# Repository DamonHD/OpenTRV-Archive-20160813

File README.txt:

WARNING: AS OF 2016/08/13 THIS IS A READ-ONLY ARCHIVE/SNAPSHOT WITH HISTORY

See https://github.com/opentrv/OTWiki/wiki/Repo-Restructure-2016-08-13
for how the content has been refactored.

This is the OpenTRV (Open-Source Thermostatic Radiator Valve) project.

See http://www.earth.org.uk/open-source-programmable-thermostatic-radiator-valve.html for more.

Contains software and hardware elements.

Note that the content of this project is available under a permissive licence,
Apache 2.0 or (Solderpad 0.51 for hardware elements) unless otherwise stated,
and is provided supplied AS-IS with no warranties of any kind.

Fragments of contributed code, libraries, etc, within here may have their own licences,
in which case that should be explicit in each case.

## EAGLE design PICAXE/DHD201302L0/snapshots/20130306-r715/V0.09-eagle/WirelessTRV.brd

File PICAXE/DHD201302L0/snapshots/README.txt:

Snapshots of software/hardware at significant development stages.

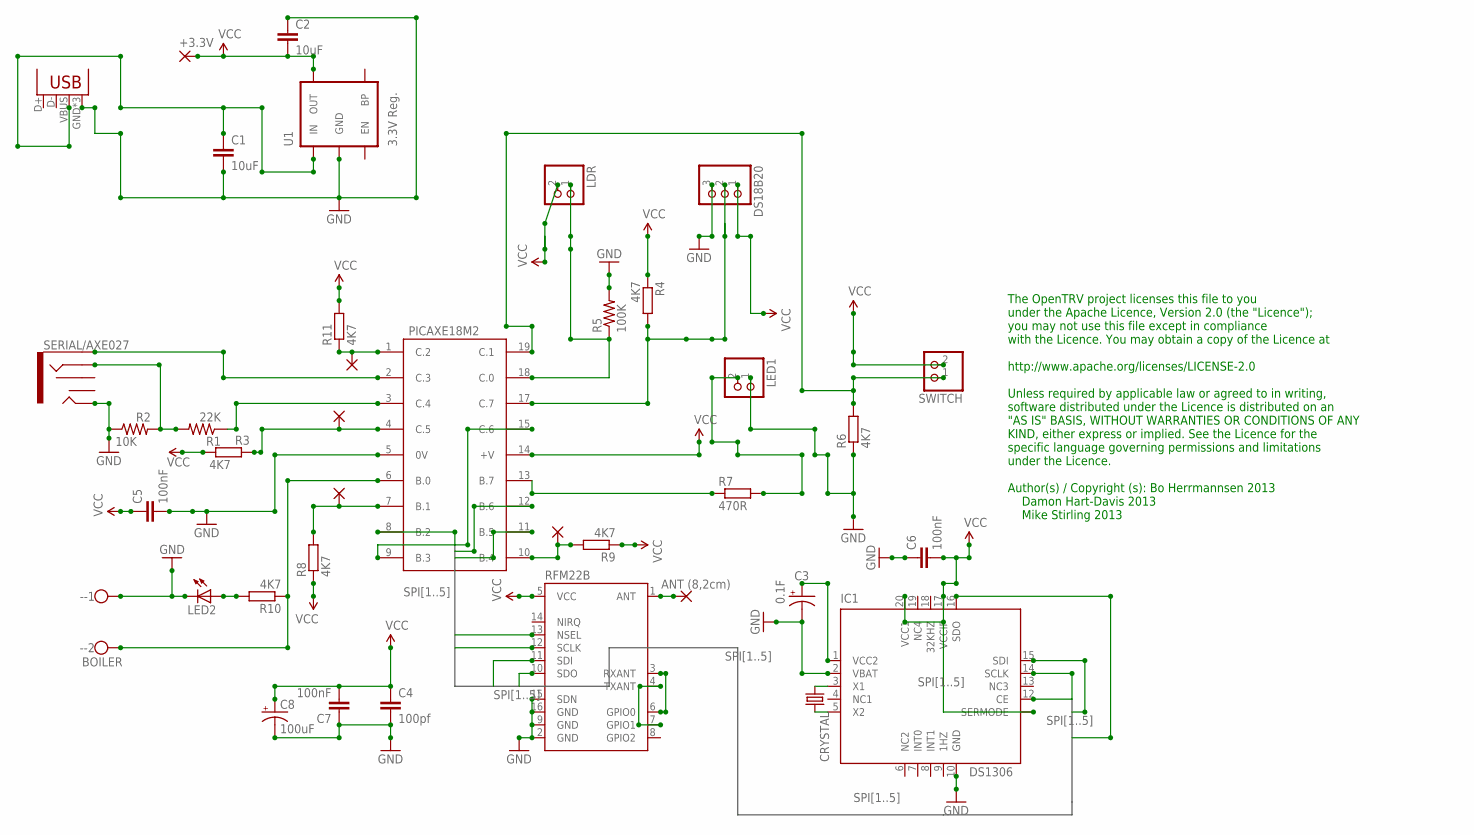
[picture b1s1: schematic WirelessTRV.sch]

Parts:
1, 4, 7, 10: 2,15/1,0
5V: USB-MICROB
+3.3V: 2,15/1,0
-: BOILER; W237-102
ANT: ANT (8,2cm); 2,15/1,0
C1, C2: 10uF; 0603-CAP
C3: 0.1F; SUPERCAP3.6V
C4: 100pf; 0603-CAP
C5, C6, C7: 100nF; 0603-CAP
C8: 100uF; EIA3216
CRYSTAL: CSM-7X-DU
DS18B20: PINHD-1X3; 1X03
IC1: DS1306
LDR: PINHD-1X2; 1X02
LED1: PINHD-1X2; 1X02
LED2: PL006-WCR12; SOT23
PICAXE18M2: PICAXE18M2
R1: 22K; 0805
R2: 10K; 0603-RES
R3, R4, R6, R8, R9, R10, R11: 4K7; M0805
R5: 100K; 1206
R7: 470R; R0603
RFM22B: RFM22SMD; RFM22-XXX-S2
SERIAL/AXE027: AUDIO-JACK2SMD; AUDIO-JACK-3.5MM-SMD
SWITCH: PINHD-1X2; 1X02
U1: 3.3V Reg.; SOT23-5

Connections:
1HZ: IC1.9 (1HZ)
32KHZ: IC1.18 (32KHZ)
GND: 5V.GND, 5V.MT1 (GND), 5V.MT2 (GND), -.1, C1.2, C2.1, C3.-, C4.2, C5.2, C6.1, C7.1, C8.C (-), DS18B20.3, IC1.2 (VBAT), IC1.10 (GND), LED1.1, LED2.3 (C), PICAXE18M2.5 (0V), R2.1, R5.2, R6.1, RFM22B.2 (GND), RFM22B.9 (GND), RFM22B.15 (SDN), RFM22B.16 (GND), SERIAL/AXE027.TIP, U1.2 (GND)
unnamed: 10.1, PICAXE18M2.10 (B.4), R9.2
unnamed: CRYSTAL.1, IC1.3 (X1)
unnamed: 4.1, PICAXE18M2.4 (C.5), R3.2
unnamed: 5V.VBUS, C1.1, U1.1 (IN)
unnamed: PICAXE18M2.2 (C.3), SERIAL/AXE027.SLEEVE
unnamed: PICAXE18M2.3 (C.4), R1.1
unnamed: R1.2, R2.2, SERIAL/AXE027.RING
unnamed: PICAXE18M2.13 (B.7), R7.1
unnamed: LED2.1 (A), R10.2
unnamed: -.2, PICAXE18M2.6 (B.0), R10.1
unnamed: 1.1, PICAXE18M2.1 (C.2), R11.1
unnamed: LED1.2, R7.2
unnamed: PICAXE18M2.19 (C.1), R6.2, SWITCH.1
unnamed: 7.1, PICAXE18M2.7 (B.1), R8.2
unnamed: CRYSTAL.2, IC1.5 (X2)
unnamed: LDR.1, PICAXE18M2.18 (C.0), R5.1
unnamed: DS18B20.2, PICAXE18M2.17 (C.7), R4.2
unnamed: RFM22B.3 (RXANT), RFM22B.6 (GPIO0)
unnamed: RFM22B.4 (TXANT), RFM22B.7 (GPIO1)
unnamed: ANT.1, RFM22B.1 (ANT)
unnamed: C3.+, IC1.1 (VCC2)
NC4: IC1.19 (NC4)
SPI1: IC1.14 (SCLK), PICAXE18M2.8 (B.2), RFM22B.12 (SCLK)
SPI2: IC1.15 (SDI), PICAXE18M2.9 (B.3), RFM22B.10 (SDO)
SPI3: IC1.16 (SDO), PICAXE18M2.15 (C.6), RFM22B.11 (SDI)
SPI4: PICAXE18M2.11 (B.5), RFM22B.13 (NSEL)
SPI5: IC1.12 (CE), PICAXE18M2.12 (B.6)
VCC: +3.3V.1, C2.2, C4.1, C5.1, C6.2, C7.2, C8.A (+), DS18B20.1, IC1.11 (SERMODE), IC1.17 (VCCIF), IC1.20 (VCC1), LDR.2, PICAXE18M2.14 (+V), R3.1, R4.1, R8.1, R9.1, R11.2, RFM22B.5 (VCC), SWITCH.2, U1.5 (OUT)

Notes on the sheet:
The OpenTRV project licenses this file to you under the Apache Licence, Version 2.0 (the "Licence"); you may not use this file except in compliance with the Licence. You may obtain a copy of the Licence at http://www.apache.org/licenses/LICENSE-2.0 Unless required by applicable law or agreed to in 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

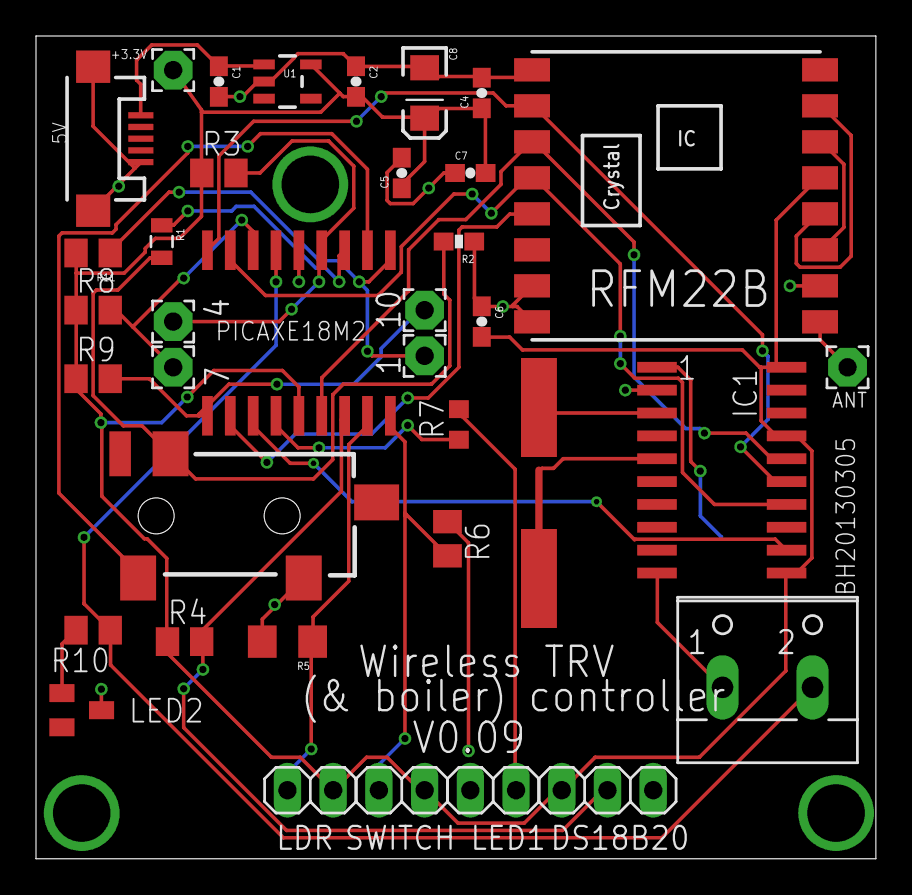
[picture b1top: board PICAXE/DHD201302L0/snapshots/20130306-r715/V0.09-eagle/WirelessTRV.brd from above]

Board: 2 copper layers, 46.7 x 45.7 mm, 38 parts (1 on the bottom side), 28 nets.

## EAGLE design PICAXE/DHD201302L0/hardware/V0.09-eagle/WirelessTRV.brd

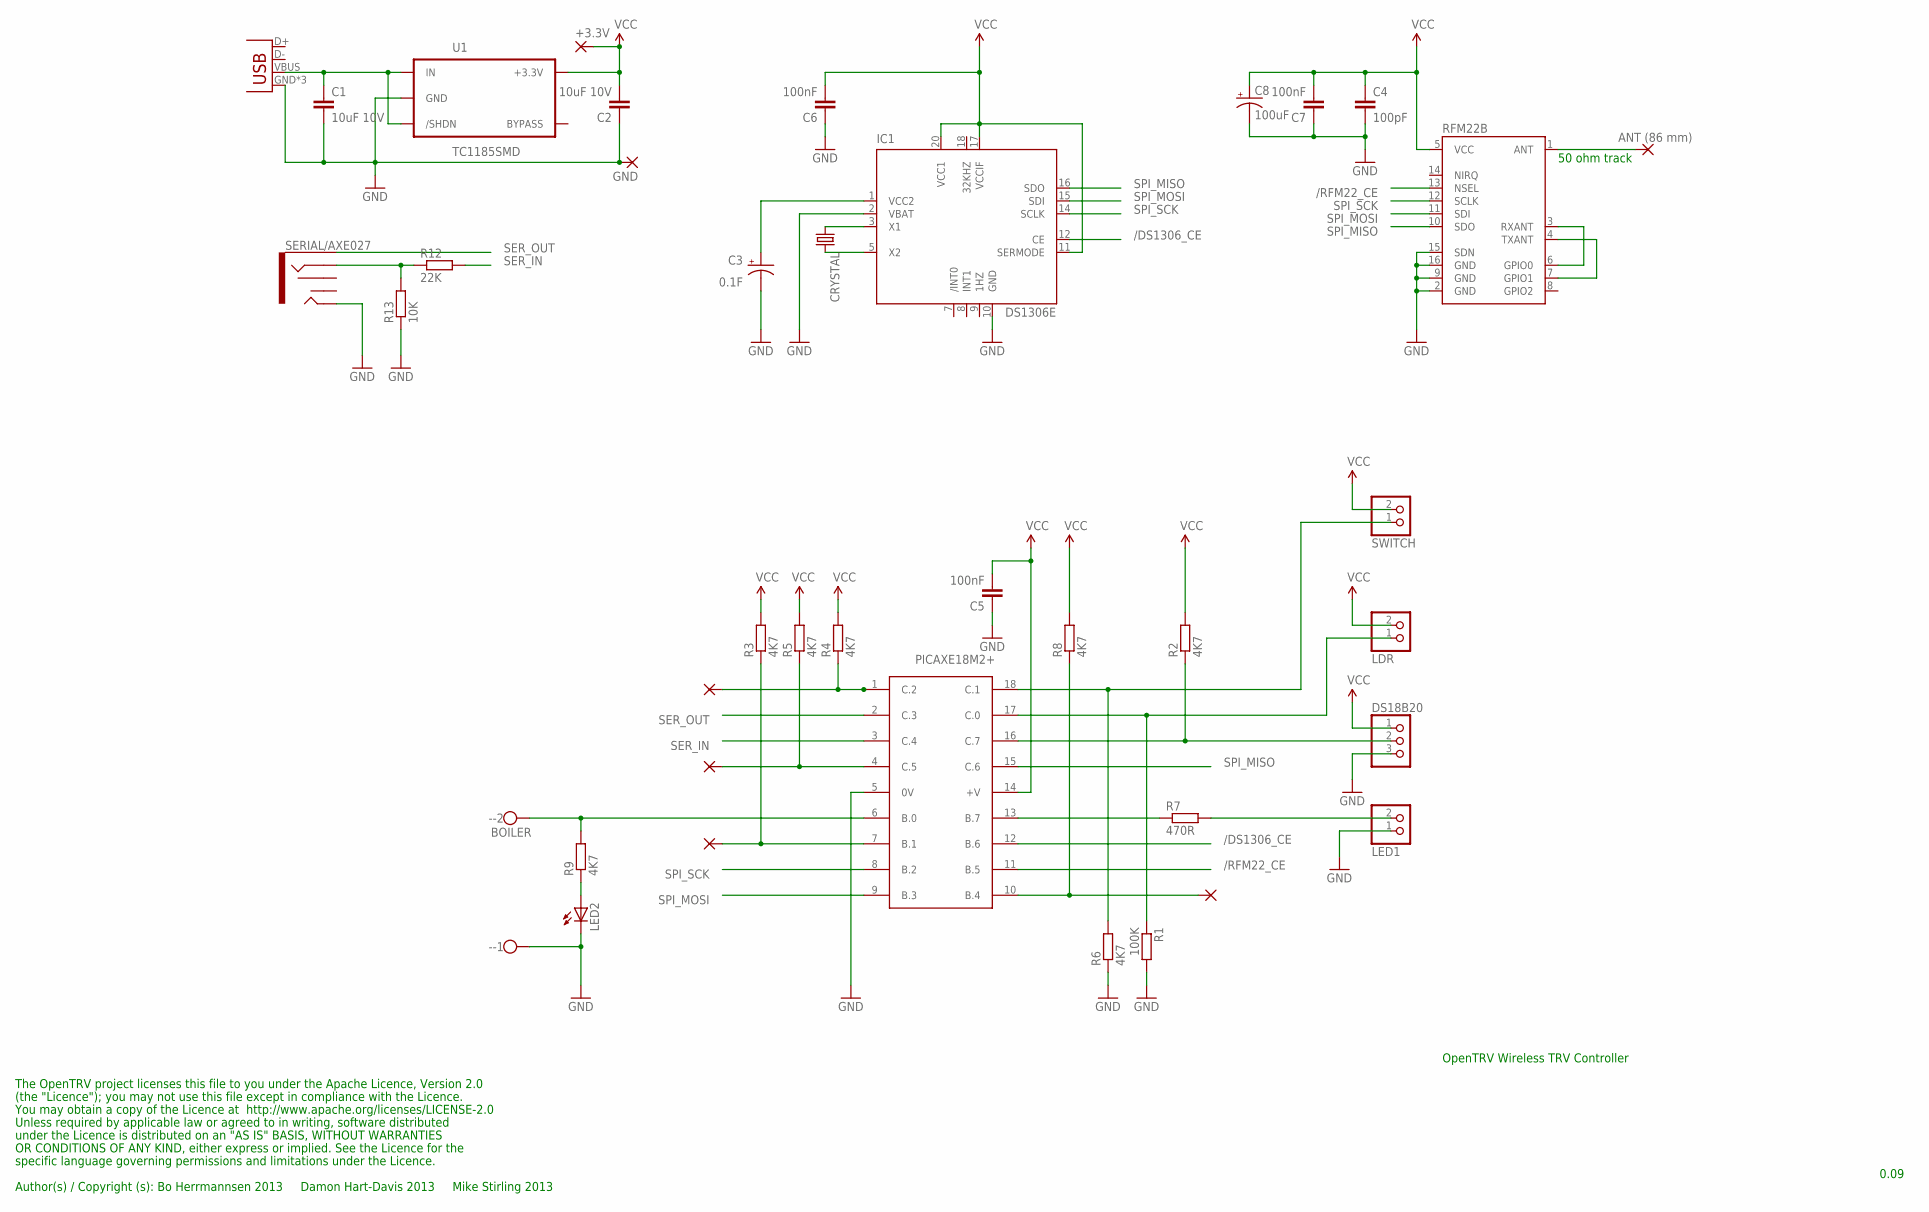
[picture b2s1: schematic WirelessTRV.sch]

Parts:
1, 4, 7, 10: 2,15/1,0
5V: USB-MICROB
+3.3V: 2,15/1,0
-: BOILER; W237-102
ANT: ANT (86 mm); 2,15/1,0
C1, C2: 10uF 10V; 0603-CAP
C3: 0.1F; SUPERCAP3.6V
C4: 100pF; 0603-CAP
C5, C6, C7: 100nF; 0603-CAP
C8: 100uF; EIA3216
CRYSTAL: MC-306
DS18B20: PINHD-1X3; 1X03
GND: 2,15/1,0
IC1: DS1306E; TSSOP20
LDR: PINHD-1X2; 1X02
LED1: PINHD-1X2; 1X02
LED2: LED2012
PICAXE18M2+: PICAXE18M2SO; SO-18W
R1: 100K; R0603
R2, R3, R4, R5, R6, R8, R9: 4K7; R0603
R7: 470R; R0603
R12: 22K; R0603
R13: 10K; R0603
RFM22B: RFM22SMD; RFM22-XXX-S2
SERIAL/AXE027: AUDIO-JACK2SMD; AUDIO-JACK-3.5MM-SMD
SWITCH: PINHD-1X2; 1X02
U1: TC1185SMD; TC1185

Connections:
/DS1306_CE: IC1.12 (CE), PICAXE18M2+.12 (B.6)
/RFM22_CE: PICAXE18M2+.11 (B.5), RFM22B.13 (NSEL)
BOILER: -.2, PICAXE18M2+.6 (B.0), R9.2
GND: 5V.GND, 5V.MT1 (GND), 5V.MT2 (GND), -.1, C1.2, C2.1, C3.-, C4.2, C5.1, C6.1, C7.1, C8.C (-), DS18B20.3, GND.1, IC1.2 (VBAT), IC1.10 (GND), LED1.1, LED2.2 (C), PICAXE18M2+.5 (0V), R1.2, R6.1, R13.1, RFM22B.2 (GND), RFM22B.9 (GND), RFM22B.15 (SDN), RFM22B.16 (GND), SERIAL/AXE027.TIP, U1.2 (GND)
LDR: LDR.1, PICAXE18M2+.17 (C.0), R1.1
LED: PICAXE18M2+.13 (B.7), R7.1
LEDEXT: LED1.2, R7.2
unnamed: 10.1, PICAXE18M2+.10 (B.4), R8.1
unnamed: CRYSTAL.1, IC1.3 (X1)
unnamed: 4.1, PICAXE18M2+.4 (C.5), R5.1
unnamed: R12.1, R13.2, SERIAL/AXE027.RING
unnamed: LED2.1 (A), R9.1
unnamed: 1.1, PICAXE18M2+.1 (C.2), R4.1
unnamed: 7.1, PICAXE18M2+.7 (B.1), R3.1
unnamed: CRYSTAL.4 (2), IC1.5 (X2)
unnamed: RFM22B.3 (RXANT), RFM22B.6 (GPIO0)
unnamed: RFM22B.4 (TXANT), RFM22B.7 (GPIO1)
unnamed: C3.+, IC1.1 (VCC2)
unnamed: 5V.VBUS, C1.1, U1.1 (IN), U1.3 (/SHDN)
unnamed: ANT.1, RFM22B.1 (ANT)
ONE_WIRE: DS18B20.2, PICAXE18M2+.16 (C.7), R2.1
SER_IN: PICAXE18M2+.3 (C.4), R12.2
SER_OUT: PICAXE18M2+.2 (C.3), SERIAL/AXE027.SLEEVE
SPI_MISO: IC1.16 (SDO), PICAXE18M2+.15 (C.6), RFM22B.10 (SDO)
SPI_MOSI: IC1.15 (SDI), PICAXE18M2+.9 (B.3), RFM22B.11 (SDI)
SPI_SCK: IC1.14 (SCLK), PICAXE18M2+.8 (B.2), RFM22B.12 (SCLK)
SWITCH: PICAXE18M2+.18 (C.1), R6.2, SWITCH.1
VCC: +3.3V.1, C2.2, C4.1, C5.2, C6.2, C7.2, C8.A (+), DS18B20.1, IC1.11 (SERMODE), IC1.17 (VCCIF), IC1.20 (VCC1), LDR.2, PICAXE18M2+.14 (+V), R2.2, R3.2, R4.2, R5.2, R8.2, RFM22B.5 (VCC), SWITCH.2, U1.5 (+3.3V)

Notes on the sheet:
50 ohm track
The OpenTRV project licenses this file to you under the Apache Licence, Version 2.0
(the "Licence"); you may not use this file except in compliance with the Licence.
You may obtain a copy of the Licence at http://www.apache.org/licenses/LICENSE-2.0
Unless required by applicable law or agreed to in writing, software distributed
under the Licence is distributed on an "AS IS" BASIS, WITHOUT WARRANTIES
OR CONDITIONS OF ANY KIND, either express or implied. See the Licence for the
specific language governing permissions and limitations under the Licence.
Author(s) / Copyright (s): Bo Herrmannsen 2013 Damon Hart-Davis 2013 Mike Stirling 2013
0.09
OpenTRV Wireless TRV Controller

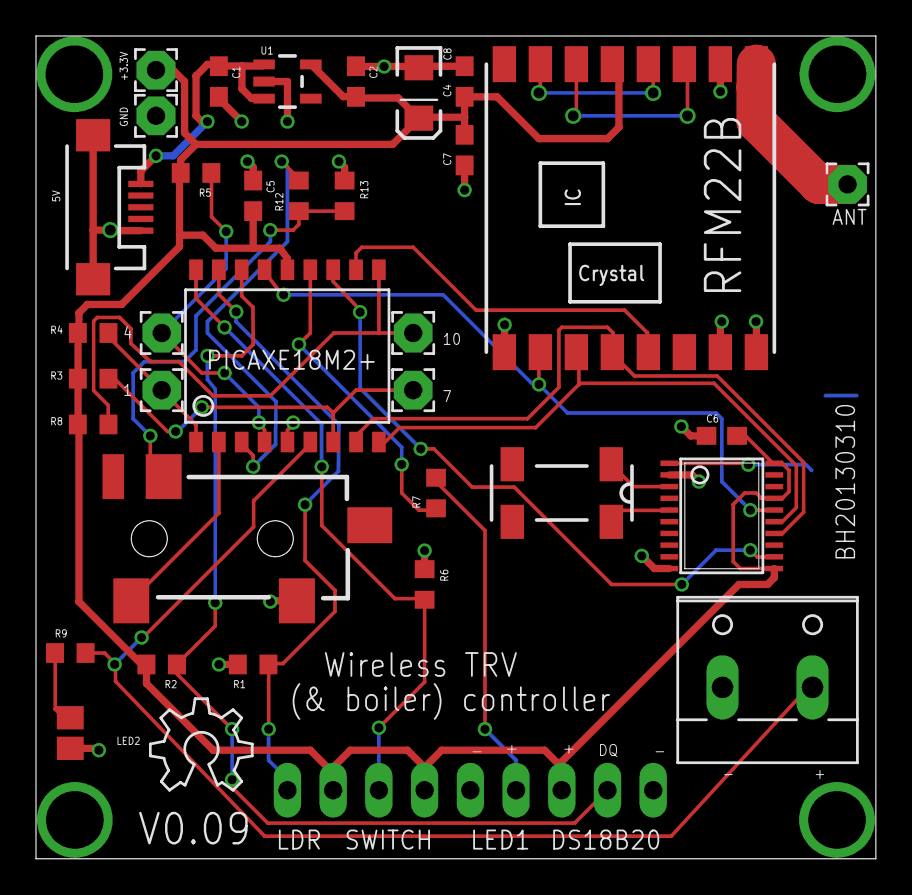
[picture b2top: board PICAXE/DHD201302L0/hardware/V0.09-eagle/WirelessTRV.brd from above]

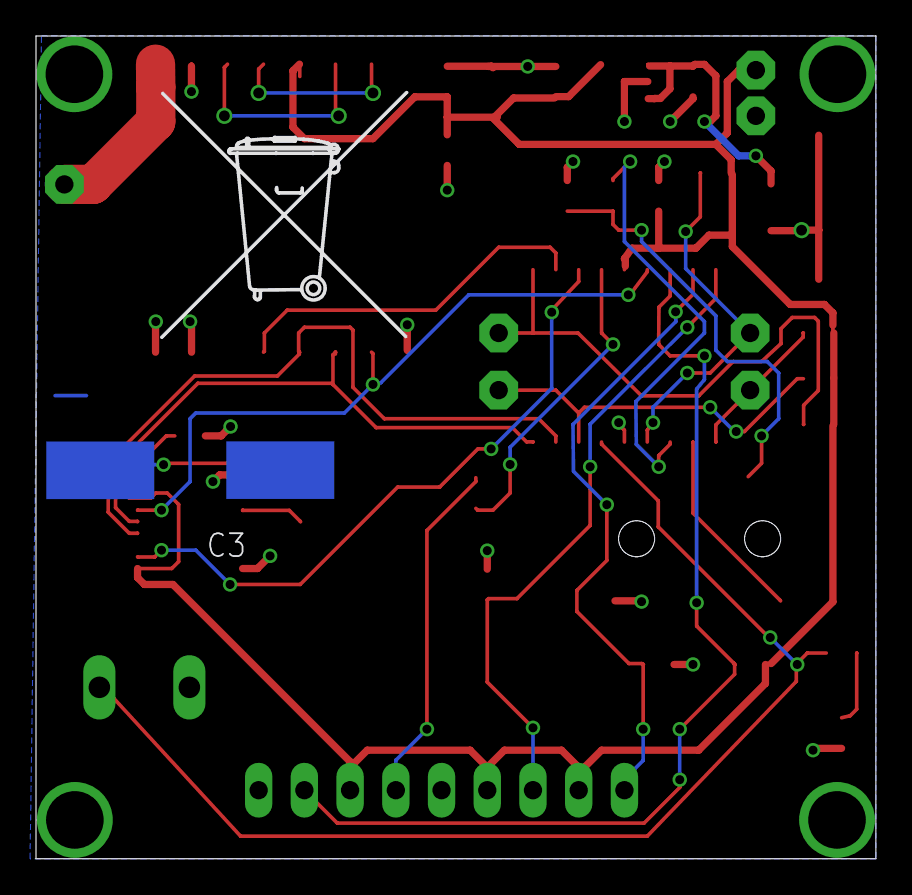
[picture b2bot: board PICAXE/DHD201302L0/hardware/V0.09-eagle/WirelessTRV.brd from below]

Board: 2 copper layers, 46.7 x 45.7 mm, 41 parts (2 on the bottom side), 28 nets.

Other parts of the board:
U$2: TONNE
U$3: OSHW_6X200_NOTEXT

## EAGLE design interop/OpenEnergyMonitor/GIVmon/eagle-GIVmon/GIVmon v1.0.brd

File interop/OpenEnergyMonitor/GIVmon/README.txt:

Eagle PCB files for GIVmon, see: http://openenergymonitor.org/emon/node/1987

(c) Bo Herrmannsen 2013 and released under the project Apache 2.0 licence
(and more permissively on request).

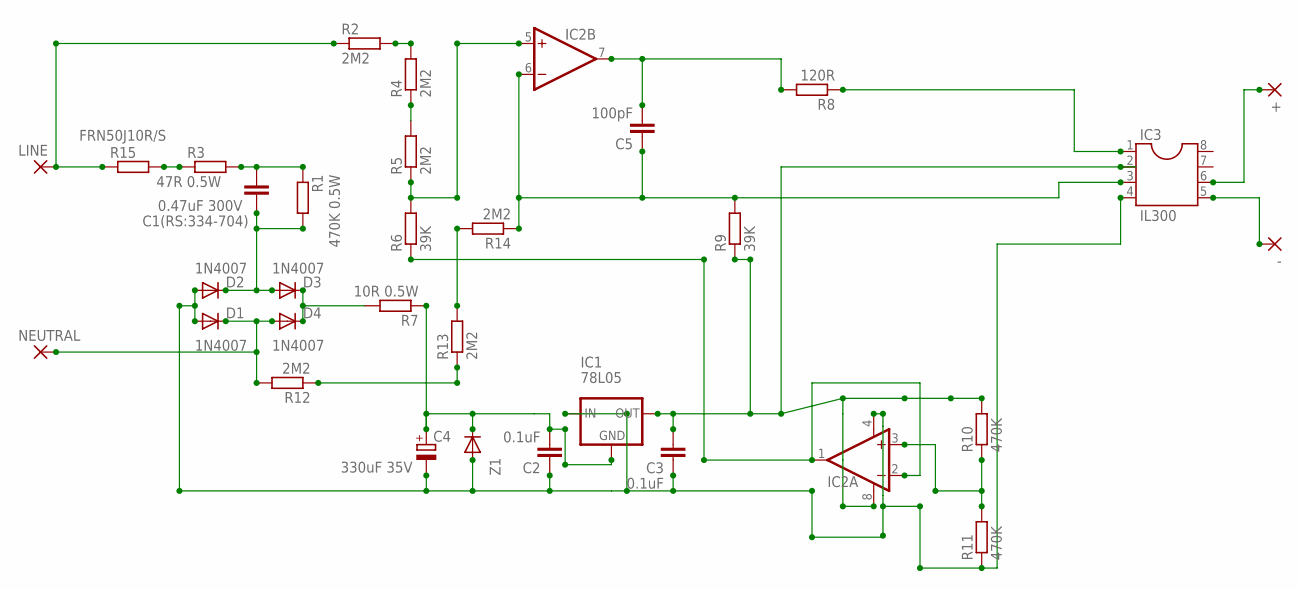
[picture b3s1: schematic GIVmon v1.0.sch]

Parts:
+: 3,81/1,4
-: 3,81/1,4
C1(RS:334-704): 0.47uF 300V; C225-108X268
C2, C3: 0.1uF; C050-024X044
C4: 330uF 35V; E5-6
C5: 100pF; C025-024X044
D1, D2, D3, D4: 1N4007; DIODE-1N4001
IC1: 78L05; TO-92
IC2: OPAMP-DUALDIP; DIP08
IC3: IL300; DIL08
LINE: 3,81/1,4
NEUTRAL: 3,81/1,4
R1: 470K 0.5W; 0204/7
R2, R4, R5, R12, R13, R14: 2M2; 0204/7
R3: 47R 0.5W; 0204/7
R6, R9: 39K; 0204/7
R7: 10R 0.5W; 0204/7
R8: 120R; 0204/7
R10, R11: 470K; 0204/7
R15: FRN50J10R/S; 0204/7
Z1: 1N59278; DIODE-1N4001

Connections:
unnamed: LINE.1, R2.1, R15.1
unnamed: D1.C, D4.A, NEUTRAL.1, R12.2
unnamed: C1(RS:334-704).2, D2.C, D3.A, R1.2
unnamed: D3.C, D4.C, R7.2
unnamed: C2.2, C4.+, IC1.1 (GND), R7.1, Z1.C
unnamed: C3.2, IC1.3 (OUT), IC2.8 (V+), IC3.2, R9.1, R10.2
unnamed: C2.1, C3.1, C4.-, D1.A, D2.A, IC1.2 (IN), IC2.4 (V-), IC3.4, R11.1, Z1.A
unnamed: C1(RS:334-704).1, R1.1, R3.2
unnamed: R2.2, R4.2
unnamed: IC2.5 (+IN), R5.1, R6.2
unnamed: R3.1, R15.2
unnamed: C5.2, IC2.7 (OUT), R8.2
unnamed: C5.1, IC2.6 (-IN), IC3.3, R9.2, R14.1
unnamed: IC2.3 (+IN), R10.1, R11.2
unnamed: -.1, IC3.5
unnamed: IC2.1 (OUT), IC2.2 (-IN), R6.1
unnamed: +.1, IC3.6
unnamed: R12.1, R13.1
unnamed: R13.2, R14.2
unnamed: IC3.1, R8.1
unnamed: R4.1, R5.2

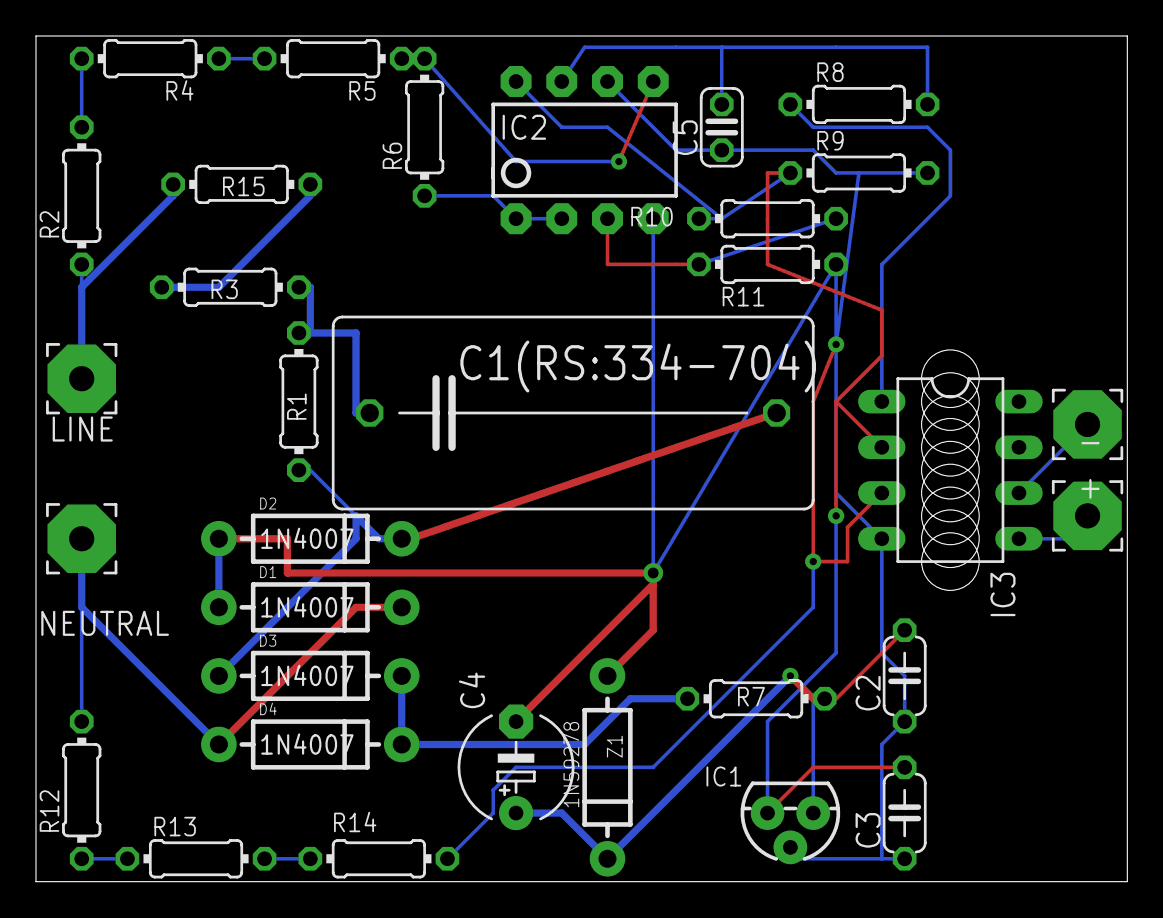
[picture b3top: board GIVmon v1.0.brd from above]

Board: 2 copper layers, 60.6 x 47.0 mm, 32 parts (0 on the bottom side), 21 nets.

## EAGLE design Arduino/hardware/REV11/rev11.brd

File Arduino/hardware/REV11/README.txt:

REV 10 is RFM23B and phototransistor and TMP112 + GSM card + boiler relay.
Dual purpose, for temporary Launchpad sensor deployment,
and as dumb-ish relay in for multiple sensors and possible device (eg boiler) control.

Note ITEADstudio .dru and .cam files downloaded from their site AND NOT COVERED BY OUR APACHE LICENCE
though ITEADstudio would probably be happy for you to use their service like we did!

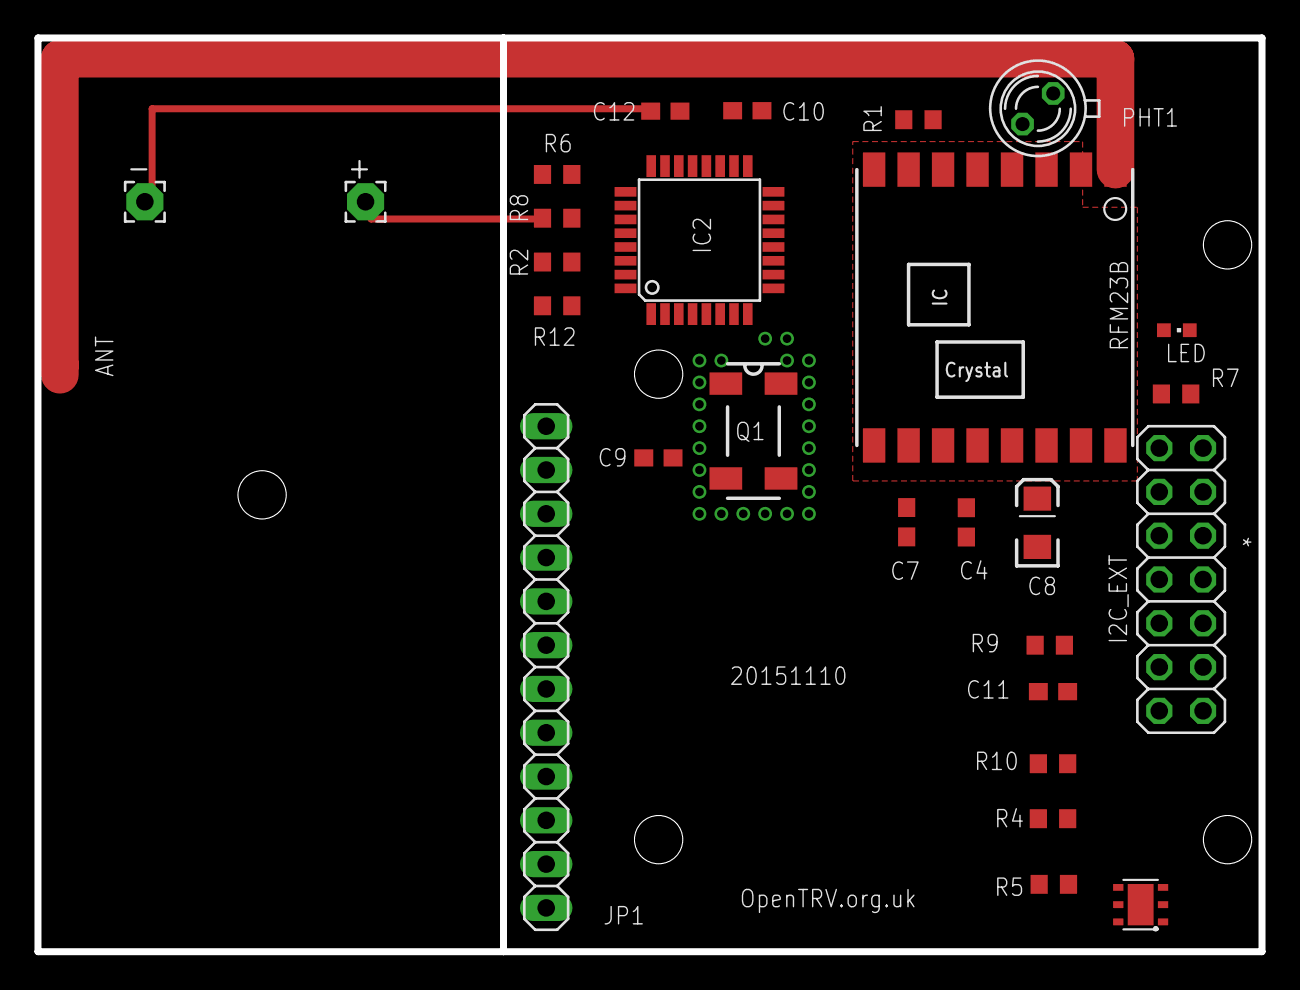
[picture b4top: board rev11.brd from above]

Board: 2 copper layers, 71.0 x 53.0 mm, 30 parts (0 on the bottom side), 34 nets.

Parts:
+: 2,15/1,0
-: 2,15/1,0
ANT: SMD1,27-2,54
C4: 100pF; C0603
C7, C9, C10, C11, C12: 100nF; C0603
C8: 100uF; EIA3216
I2C_EXT: 2X07
IC2: ATMEGA168-AU; TQFP32-08
JP1: 1X12
LED: CHIPLED_0603
PHT1: BPX65
Q1: 32768Hz; MC-306
R1: 100K; R0603
R2, R4, R5, R6, R8, R9, R12: 4.7K; R0603
R7: 470R; R0603
R10: 1K; R0603
RFM23B: RFM23B; RFM23-XXX-S1
U$1: OSHW_10X200_NOTEXT
U$2: TONNE
U$4: SHT21

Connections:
A1: IC2.24, JP1.1
A2: IC2.25, JP1.2
A3: IC2.26, JP1.3
A6: IC2.19, JP1.4
A7: IC2.22, JP1.5
D2: IC2.32, JP1.10, R9.1
D3: IC2.1, JP1.6
D5: IC2.9, JP1.7
D6: IC2.10, JP1.8
D7: IC2.11, JP1.9
GND: -.1, C4.1, C7.2, C8.C, C9.2, C10.2, C12.2, I2C_EXT.6, IC2.3, IC2.5, IC2.21, JP1.12, R1.2, RFM23B.2, RFM23B.9, RFM23B.15, RFM23B.16, U$4.2, U$4.P$1
IO_POWER_UP: IC2.12, PHT1.A
LDR: IC2.23, PHT1.K, R1.1
LED_HEATCALL_L: IC2.2, R7.1
unnamed: C11.2, I2C_EXT.5
unnamed: I2C_EXT.12, R5.2
unnamed: I2C_EXT.11, R4.2
unnamed: C12.1, IC2.20
unnamed: R10.2, RFM23B.14
unnamed: LED.C, R7.2
unnamed: ANT.1, RFM23B.1
RESET: C11.1, IC2.29, R2.2
RFM_IRQ: I2C_EXT.7, IC2.13, R10.1
RX: IC2.31, R4.1
SCL: I2C_EXT.9, IC2.28, R8.1, U$4.6
SDA: I2C_EXT.10, IC2.27, R6.2, U$4.1
SPI_MISO: I2C_EXT.1, IC2.16, RFM23B.10
SPI_MOSI: I2C_EXT.4, IC2.15, RFM23B.11
SPI_NSS: I2C_EXT.8, IC2.14, R12.1, RFM23B.13
SPI_SCK: I2C_EXT.3, IC2.17, RFM23B.12
TX: IC2.30, R5.1
VCC: +.1, C4.2, C7.1, C8.A, C9.1, C10.1, I2C_EXT.2, IC2.4, IC2.6, IC2.18, JP1.11, LED.A, R2.1, R6.1, R8.2, R9.2, R12.2, RFM23B.5, U$4.5
XTAL1: IC2.8, Q1.4
XTAL2: IC2.7, Q1.1

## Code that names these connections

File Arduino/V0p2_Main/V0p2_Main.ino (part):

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    * 1MHz CPU clock (from 8MHz internal RC clock with /8 prescaler) ATmega328P running at 1.8V--5V (typically 2V--3.3V).
    * Fuse set for BOD-managed additional clock settle time, ie as fast a restart from sleep as possible.
    * All unused pins unconnected and nominally floating (though driven low as output where possible).
    * 32768Hz xtal between pins XTAL1 and XTAL2, async timer 2, for accurate timekeeping and low-power sleep.
    * All unused system modules turned off.

  Basic AVR power consumption ticking an (empty) control loop at ~0.5Hz should be ~1uA.
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#ifdef LED_HEATCALL
  pinMode(LED_HEATCALL, OUTPUT);
#else
  pinMode(LED_HEATCALL_L, OUTPUT);
#endif
  for( ; ; )
    {
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
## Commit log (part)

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2016-02-13 TODO-721: doing successful association lookup
2016-02-14 TODO-721: WIP
    Non-secure JSON stats TX seems to be OK,
    but RX seems to be off-by-1.
2016-02-14 TODO-721: apparently fixed TX issue
    Forcing constraint on JSON max size.
2016-02-14 TODO-721: moar debugging
    On secure side this time.
2016-02-14 TODO-721: can synthesise @ and + fields
2016-02-14 TODO-721: WIP
    Beacon off.
    Synthetic full node ID on own stats.
    Turning off some debug.
2016-02-14 TODO-721: slight rearrangement for clarity
2016-02-14 TODO-747: tweaking DORM1 UI
2016-02-14 improved comments
2016-02-14 D21FM: zapping COMMON_SETTINGS
2016-02-14 Renamed CONFIG_REV10_ASRELAY
2016-02-14 Renamed REV10 relay and phototransistor defines
2016-02-14 D21FM: moving stuff down to lib
2016-02-14 TODO-721: squeezing... 33384 bytes
2016-02-14 TODO-721: builds fine for secure and not
2016-02-14 TODO-798: sending the valve position
    Will be needed the moment we install a boiler unit
    with secure frames.
2016-02-15 prep for release and branch
2016-02-15 First micro fixes on patch branch...
2016-02-15 Adjusting 'O' frame spec.
2016-02-16 TODO-721: standardising and trimming RX error msgs
2016-02-16 Probationary Xtal sanity check
2016-02-16 TODO-721: WIP
2016-02-17 TODO-801: first attempt to reduce overrun risk
2016-02-19 Better use of sleep before stats TX.
2016-02-20 TODO-721: timing for message processing
2016-02-20 TODO-747: WIP
2016-02-20 Energy-saving tweak for LEARNed programmes
2016-02-20 tidyup
2016-02-22 Moved REV14 configs out to libs
2016-02-22 Fixed Occupancy compilation error
2016-02-22 Fixed compilation bug for expand and compress temperature
2016-02-22 Added CONFIG_REV14 description
2016-02-22 Added CONFIG_REV14 power consumption figure
2016-02-22 D21FM: moving REV5 configs down
2016-02-23 typos
2016-02-24 rough rev 15
2016-02-25 rev16
    rough power board
2016-02-25 files renamed
2016-02-25 new structure
2016-02-25 20160131-COHEAT-dual-channel-beta4 update
2016-02-26 up to rev18 roughly
2016-02-26 up to rev18 cleaned up
2016-02-26 Keep git/Eagle from fighting.
2016-02-26 up to rev18 DRC check and ground plane
2016-02-26 D21FM: moving stuff down to the library
    May have borked something since several configs
    now result in 'too big' builds.
2016-02-28 REV15-18 cleaned up, need sanity check
2016-03-01 rev15-18 changed as per Deniz suggeastions
2016-03-01 Initial implementation, needs to be tested on live system (BG home RPi)
2016-03-01 set CONFIG_REV14
2016-03-01 Upped version
2016-03-01 Fixed example payload in documentation
2016-03-01 Added config unit test
2016-03-01 Corrected comment
2016-03-02 Adjusting panic() with message for clarity.
2016-03-02 TODO-841: WIP
2016-03-02 TODO-844: moved xtal check down
2016-03-02 ic2_ext labels closer to connector
2016-03-02 TODO-843: enable cap on JSON length
2016-03-02 .small fix
2016-03-02 TODO-841: text 16WW REV2 lvbh k
2016-03-02 TODO-841: text 16WW REV4
2016-03-03 Added FTDI label to board as per deniz advice
2016-03-03 Fixed C16 sensor ID
2016-03-03 Added REV15 gerbers + readme etc. Waiting on Bo for BOM
2016-03-04 TODO-721: WIP
    Adjusting to new structure.
2016-03-04 TODO-721: spec update for replay attack robustness
2016-03-05 TODO-728: squeezing code into relay
2016-03-05 TODO-728: too big!
2016-03-05 TODO-728: nearly fits!
2016-03-05 TODO-728: fits!
2016-03-05 TODO-728: trimming code
2016-03-06 TODO-721: ready to merge...
2016-03-06 TODO-728: being clear about security risks
2016-03-06 TODO-728: switched to decodeSecureSmallFrameSafely()
2016-03-07 TODO-728: providing some RX auth failure diagnostics
2016-03-07 TODO-721: preparing for DORM1/REV10 release
    Also, making traffic analysis of encrypted frames harder.
2016-03-07 Slightly re-arranged for efficiency.
2016-03-07 TODO-721: report if TX key not available
2016-03-07 trimming code space
2016-03-09 TODO-786: WIP
2016-03-09 More clock stabilise time before radio(s) init...
2016-03-09 test REV2 secure NOHUB for TX range
2016-03-09 test REV2 secure STATSHUB for TX range
2016-03-09 trimming code
2016-03-10 TODO-786
2016-03-10 TODO-786: initial tests OK
2016-03-10 First draft code structure
2016-03-10 Extended structural code
2016-03-10 TODO-721: slightly reducing 'decoy' traffic
    Slightly too much extra bandwidth being used by eye.
2016-03-10 Added tests and topic path
2016-03-10 Added initial MQTT tests and debugged corresponding code
2016-03-11 Trying to allow stats TX from REV10 again.
2016-03-11 Added package files to simplify testing
2016-03-11 Added package file to make top level a package
2016-03-11 Added a short paragraph on running tests
2016-03-11 TODO-851: make secondary radio panic explicit
2016-03-11 Tested nested topic when priting record
2016-03-11 Added command line options to concentrator code
2016-03-11 Updated default root topic to match the Java MQTT handler
2016-03-11 TODO-851: REV10 TXing own stats again
2016-03-11 Fixed failing MQTT test
2016-03-11 TODO-851
2016-03-11 Implemented and tested SenML serializer
2016-03-11 Added inline documentation
2016-03-12 Tested MQTT on_message and fixed
2016-03-14 Added Vagrantfile to bring up clean VM for testing
2016-03-14 Added bootstrap script
2016-03-14 Added install scripts and python requirements file
2016-03-14 Made install.sh executable
2016-03-14 Debugged basic loop
2016-03-14 Added basic error handling on commissioning
2016-03-14 Added initial Flask hello world
2016-03-14 Added mosquitto-clients to the install to make it easier to test
2016-03-14 Cleaned up HTTP client code
2016-03-15 Fixed MQTT tests
2016-03-15 Added small storage library
2016-03-15 TODO-728: squeezing REV10 image
2016-03-15 Added simple model
2016-03-15 Renamed Devices into Concentrators to keep naming consistent
2016-03-15 Added teafiles libreary
2016-03-15 Added option to truncate topic
2016-03-15 Added Devices model and fixed error in MQTT tests
2016-03-15 Added initial record processing loop with device handling
2016-03-15 Added Sensors model
2016-03-15 Added sensor handling in post
2016-03-16 TODO-861: WIP
2016-03-16 Allow for xxx.xxx.xxx.xxx max length IPv4 addr.
2016-03-16 REV14 hardware test
2016-03-16 Added correct file
2016-03-16 removed incorrect file
2016-03-16 TODO-851: WIP: ENABLE_JSON_FRAME_MINIMISED
2016-03-16 D21FM: moving stuff down to the libraries
2016-03-16 COH-71: starting
2016-03-16 COH-71: new bare sketch
2016-03-16 COH-71: WIP
2016-03-16 typo
2016-03-16 Added Series model and value storage
2016-03-16 Added simple GET endpoints
2016-03-16 Updated the install.sh script to handle vagrant VM or local install
2016-03-16 Added setup support
2016-03-16 Changed name of python package and removed unnecessary egg output from .gitignore
2016-03-16 Updated install script to handle install on non-vagrant system (e.g. on a Pi)
2016-03-17 Added SenML MIME type
2016-03-17 Fixed SenML format to confirm to spec 04 (ver: 3)
2016-03-17 Added write support for Hypercat
2016-03-17 D21FM: moving more of the FHT8V code to lib
2016-03-17 Reworked GET API into Hypercat implementation
2016-03-17 Added license header to all files
2016-03-17 D21FM: WIP: moving CLI core down...
2016-03-17 D21FM: CLI API simplification
2016-03-17 COH-71
2016-03-18 Changed option prog argument to improve the -h output
2016-03-19 COH-71: bringing in sensor definition
2016-03-19 COH-71: making FHT8V getHCx() ISR- safe
2016-03-22 CPH-71
2016-03-22 COH-71: design doc
2016-03-22 COH-71: design docs
2016-03-23 COH-77: WIP
2016-03-23 COH-77: simple serial status for REV9/relay
2016-03-23 COH-77: for Marko to toy with
2016-03-25 COH-80: WIP
2016-03-25 COH-81: WIP
2016-03-25 COH-80: improved doc
2016-03-25 COH-80: doc
2016-03-25 test
2016-03-25 refrob
2016-03-26 COH-80: all messages flowing, but lossy
2016-03-26 TODO-867: COH-80: WIP
    Trying to ensure progress on RX queue
    in preference to CLI (and other slow work)
    where there is potential conflict.
2016-03-26 COH-80
2016-03-26 COH-80: design doc
2016-03-26 expunging COHEAT from main line
2016-03-27 DS18B20 tidyup
2016-03-27 COH-71: selecting correct (minimum) DS18B20 precision
2016-03-27 tweaked DS18B20 code seems to work on REV9
2016-03-27 doc fix
2016-03-27 COH-71: doc fix
2016-03-27 COH-71: making compile when non-secure
2016-03-28 COH-71: RX counter wear
2016-03-30 Added commissioning message process details
2016-03-30 Clarified suggested functional extensions
2016-03-31 release procedure
2016-03-31 typo fix
2016-03-31 snapshot of underlying libs for 20160331-COHEAT-M1-1.0.0
2016-03-31 sample compilation test for DORM1
    (Note: various builds are over-size at the moment.)
2016-04-05 adjust UI LED flashes to work consistently w/no light sensor
2016-04-06 added rev11 secure statshub config
2016-04-11 TODO-887: WIP
2016-04-13 TODO-887: watchdog nominally installed
    Testing...
2016-04-13 TODO-887: turning off explicit overrun detection
    Testing...
2016-04-14 fixed rev10 transistor
2016-04-15 TODO-887: testing w/ secure comms on DORM1
2016-04-15 Disabling initial CLI activation on boot.
    Avoids stealing time from other things at startup
    such as valve calibration.
    CLI can be activated with any character on the input line.
2016-05-04 getElapsedSecondsLT()
2016-05-04 COHEAT-M2 start
2016-05-05 COHEAT-M2 bugfix
2016-05-05 COHEAT-M2 all libs same except OTRadioLink
2016-05-05 snapshot 1.1.0 release of OTRadioLink
2016-05-16 Fixed sim900 declaration
2016-05-16 fixed udp address
2016-05-17 ETV test case data samples 2016/03 16WW
2016-05-17 fixing MQTT lib path
2016-05-18 TODO-897: WIP
2016-05-20 TODO-897: extra (better) test data set for ETV
2016-06-08 Added secure stats relay and boiler hub config
2016-06-21 TODO-897: ETV support
2016-07-06 TODO-897: splitting input API ready to process data format as supplied
2016-07-06 TODO-897: TDD
2016-07-07 TODO-897
2016-07-07 TODO-897: tested sample interval calc
2016-07-08 TODO-897: verifying correct sample choice
2016-07-08 TODO-897: testing correct behaviour around DST switch to match HDD
2016-07-09 TODO-897: factoring out HDD collection interface
2016-07-12 TODO-987: testing NBulkKWHParseByID.extractIDs()
2016-07-12 TODO-906: introduced end of day tasks and made the update one of them
2016-07-13 TODO-897: improved comments
2016-07-13 TODO-897: filling out simple case
2016-07-13 TODO-897: extending ETVPerHouseholdComputationInput with house ID
2016-07-14 TODO-897: ETVPerHouseholdComputationSimpleImpl start
2016-07-22 debugging info
2016-07-22 REV10 PDF copy.
2016-08-03 TODO-897: HDD data as downloaded
2016-08-03 TODO-897: format simplified
2016-08-03 TODO-897: extra data trimmed
2016-08-03 TODO-897: test load of 2016H1 HDD data set
2016-08-03 TODO-897: test class rename for clarity
2016-08-03 TODO-897: extended gas kWh sample
2016-08-03 TODO-897: bigger bulk kWh home heat data set
2016-08-03 TODO-897: testing load of larger data set
2016-08-04 cleaned up debug output
2016-08-04 more debug cleaning
2016-08-04 TODO-897: ETV simple computation TDD
2016-08-04 TODO-897: computation TDD
2016-08-04 TODO-897: simple computation TDD
2016-08-04 selected geosim
2016-08-06 TODO-897: refactoring (interface name improvement)
2016-08-06 TODO-897: work on bulk extraction across many households
2016-08-07 TODO-897: multi-computation WIP
2016-08-07 TODO-897: more lambda friendly
2016-08-07 walrus and motor driver eval
2016-08-08 TODO-897: ETVPerHouseholdComputationResultToCSV
2016-08-10 png's as requested by deniz
2016-08-10 TODO-897: output TDD
2016-08-10 TODO-897: ouput TDD
2016-08-12 Added default value for min boiler on minutes.
2016-08-12 removed boiler debugging
2016-08-12 added documentation
2016-08-12 fixes for Arduino AVR boards v1.6.12

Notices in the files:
Arduino/hardware/REV11/rev11.brd:
License: http://goo.gl/3d71UJ
parts and their libraries:
SparkFun-Passives: Licensing: CC v3.0 Share-Alike You are welcome to use this library for commercial purposes.
